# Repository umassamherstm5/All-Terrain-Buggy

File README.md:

# All-Terrain-Buggy
The All-Terrain Buggy is a buggy that goes on most if not all terrains. 

It is a 6-wheeled AWD remote controlled vehicle. The motors are driven by the DRV8871 motor drivers. 
The buggy is controlled via a FlySky remote that feeds PWM signals into an Adafruit Feather 328P MCU.  

This project contains the firmware for the Feather 328P and all KiCad files for the buggy's custom PCB.

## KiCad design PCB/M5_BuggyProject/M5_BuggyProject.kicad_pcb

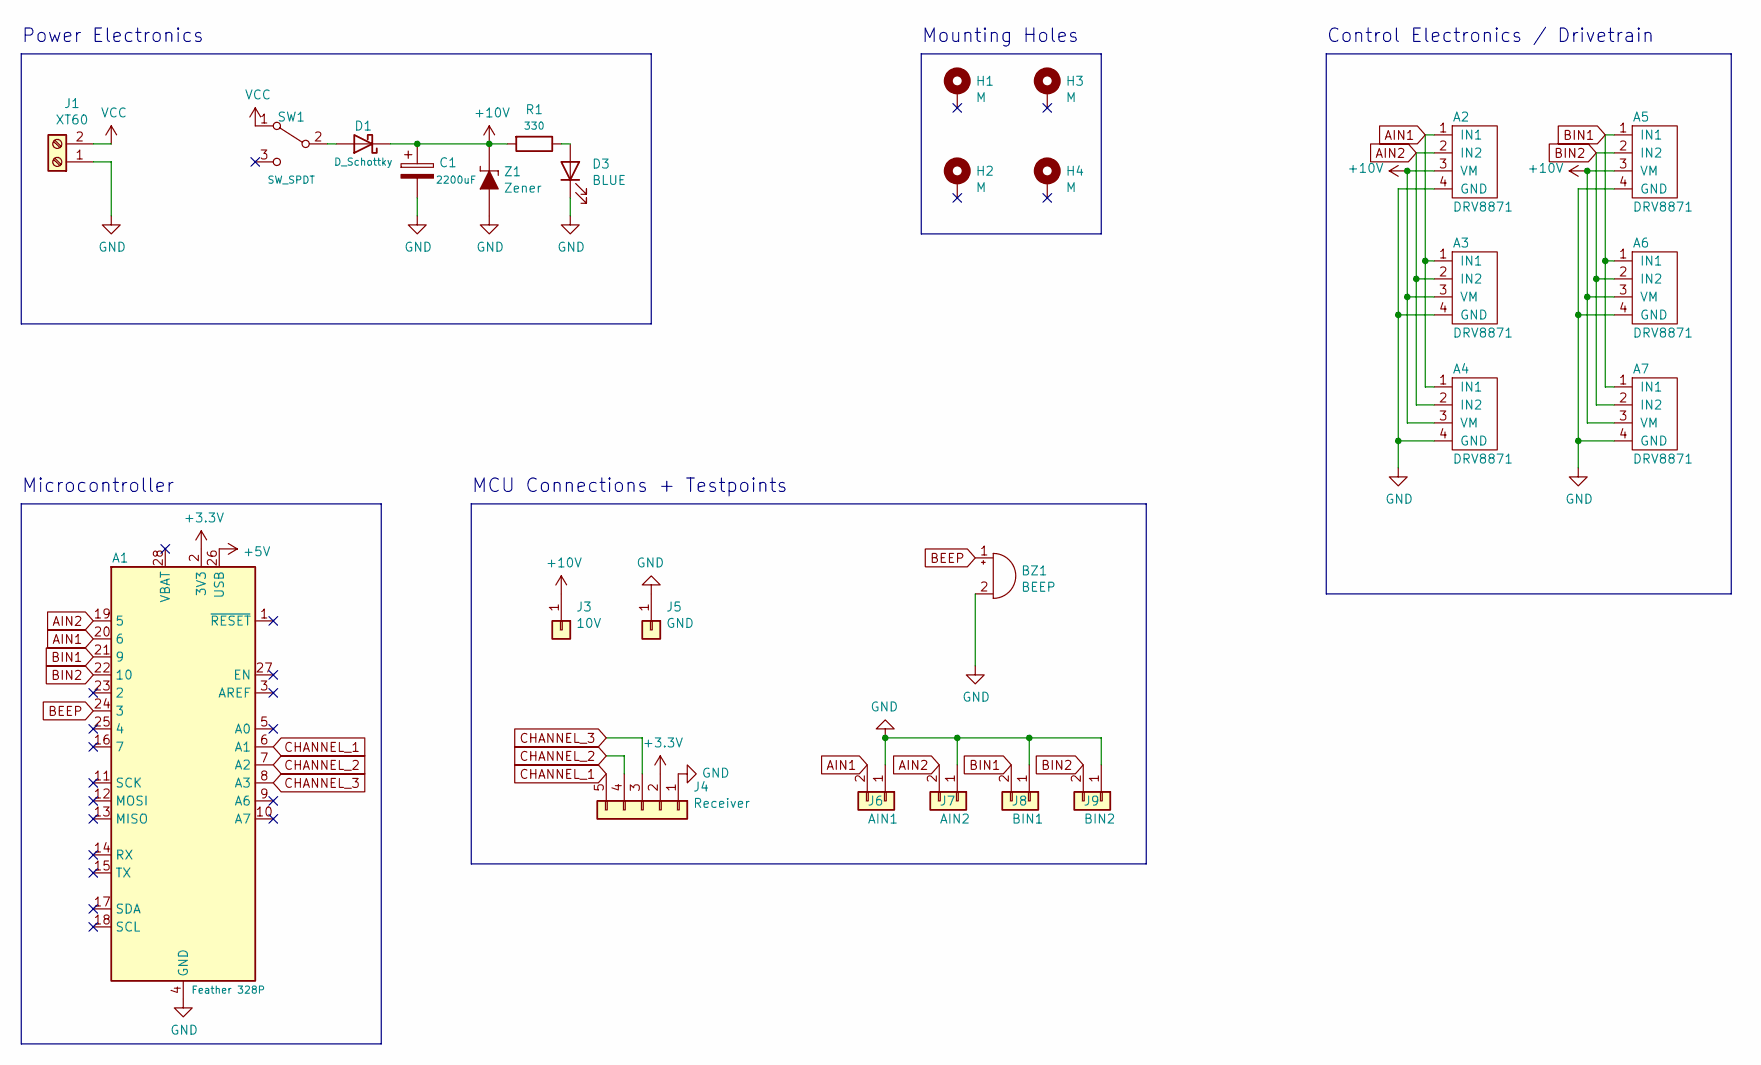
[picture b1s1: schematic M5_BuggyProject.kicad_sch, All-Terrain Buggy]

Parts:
A1: Feather 328P; Adafruit_Feather
A2, A3, A4, A5, A6, A7: DRV8871; PinSocket_1x04_P2.54mm_Vertical
BZ1: BEEP; Buzzer_12x9.5RM7.6
C1: 2200uF; CP_Radial_D10.0mm_P5.00mm
D1: D_Schottky; TO-220-2_Vertical
D3: BLUE; LED_1206_3216Metric
H1, H2, H3, H4: M; MountingHole_4.3mm_M4_Pad_Via
J1: XT60; AMASS_XT60-M_1x02_P7.20mm_Vertical
J3: 10V; TestPoint_Plated_Hole_D5.0mm
J4: Receiver; PinSocket_1x05_P2.54mm_Vertical
J5: GND; TestPoint_Plated_Hole_D5.0mm
J6: AIN1; PinSocket_1x02_P2.54mm_Vertical
J7: AIN2; PinSocket_1x02_P2.54mm_Vertical
J8: BIN1; PinSocket_1x02_P2.54mm_Vertical
J9: BIN2; PinSocket_1x02_P2.54mm_Vertical
R1: 330; R_1206_3216Metric
SW1: SW_SPDT; 1101M2S3CQE2
Z1: Zener; DO-214AC; MPN 1N5231BTR; Digi-Key_PN 1N5231BFSCT-ND

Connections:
+3V3: A1.2 (3V3), J4.2
+5V: A1.26 (USB)
+10V: A2.3 (VM), A3.3 (VM), A4.3 (VM), A5.3 (VM), A6.3 (VM), A7.3 (VM), C1.1, D1.1 (K), J3.1, R1.2, Z1.K
AIN1: A1.20 (6), A2.1 (IN1), A3.1 (IN1), A4.1 (IN1), J6.2
AIN2: A1.19 (5), A2.2 (IN2), A3.2 (IN2), A4.2 (IN2), J7.2
BEEP: A1.24 (3), BZ1.1 (-)
BIN1: A1.21 (9), A5.1 (IN1), A6.1 (IN1), A7.1 (IN1), J8.2
BIN2: A1.22 (10), A5.2 (IN2), A6.2 (IN2), A7.2 (IN2), J9.2
CHANNEL_1: A1.6 (A1), J4.5
CHANNEL_2: A1.7 (A2), J4.4
CHANNEL_3: A1.8 (A3), J4.3
GND: A1.4 (GND), A2.4 (GND), A3.4 (GND), A4.4 (GND), A5.4 (GND), A6.4 (GND), A7.4 (GND), BZ1.2 (+), C1.2, D3.1 (K), J1.1, J4.1, J5.1, J6.1, J7.1, J8.1, J9.1, Z1.A
unnamed: D1.2 (A), SW1.2 (B)
unnamed: D3.2 (A), R1.1
VCC: J1.2, SW1.1 (A)

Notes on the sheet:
MCU Connections + Testpoints
Control Electronics / Drivetrain
Power Electronics
Mounting Holes
Microcontroller

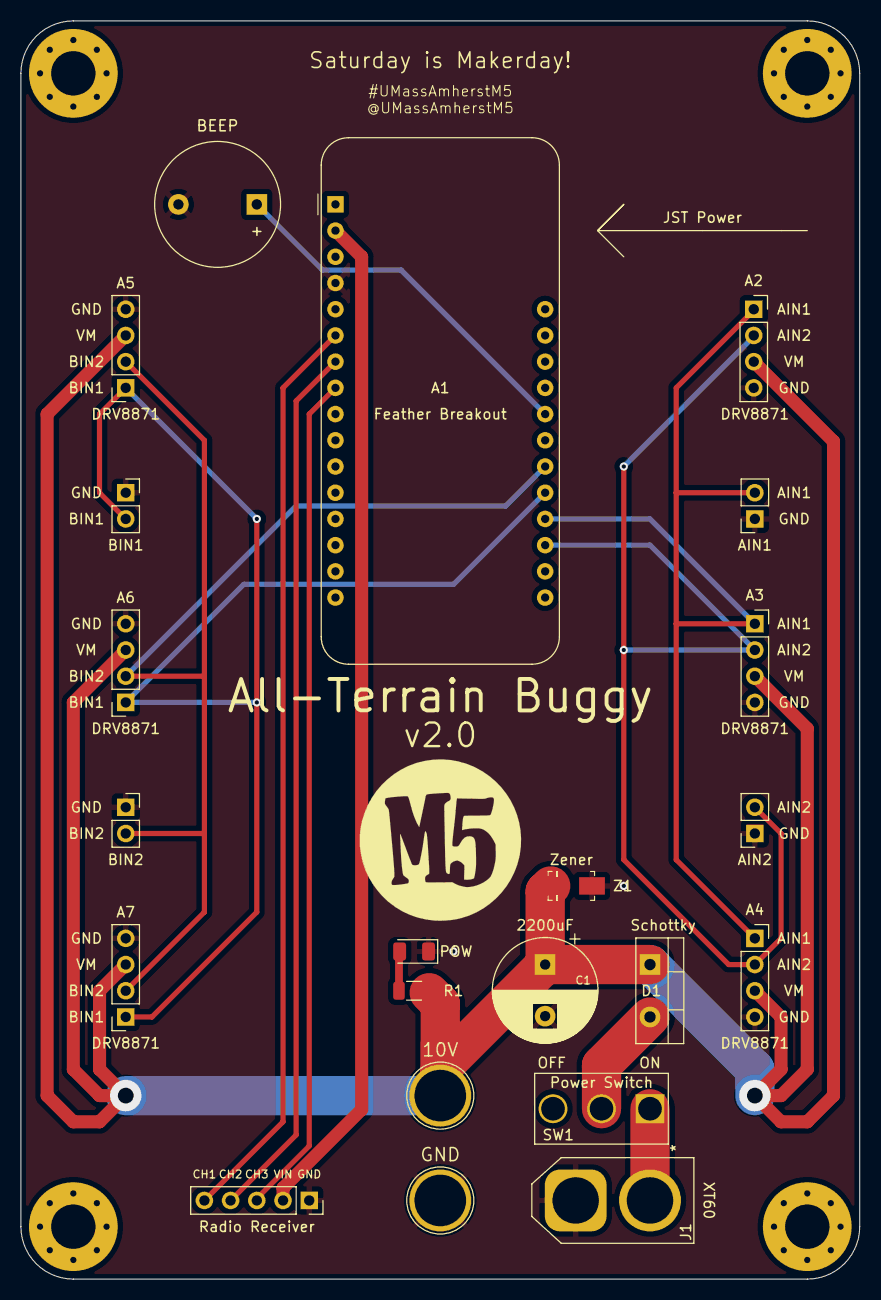
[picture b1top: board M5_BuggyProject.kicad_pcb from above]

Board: 2 copper layers, 81.3 x 121.9 mm, 26 parts (0 on the bottom side), 14 nets.

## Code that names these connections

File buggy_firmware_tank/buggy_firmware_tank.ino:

/*
 * All-Terrain Buggy
 * Firmware for interfacing with buggy and remote control 
 * Tank mode: each joystick controls each side
 * Authors: Akshat Sahay, Chris Caron, Sebastian Armstrong 
 */

/*
 * FlySky FS-GT
 * ------------
 * The FlySky FS-GT is a radio receiver module which pairs to a FlySky hobbyist controller. 
 * 
 * We connect this receiver to our Feather 328P and read the pulses on different channels using the pulseIn function. 
 * CHANNEL_1 refers to the left joystick's vertical motion. 
 * CHANNEL_2 refers to the right joystick's horizontal motion. 
 * CHANNEL_3 refers to the right pot 
 */

/* pin assignments for FlySky receiver signals */
#define CHANNEL_1 A1 // controller CH2  
#define CHANNEL_2 A2 // controller CH3
#define CHANNEL_3 A3

/*
 * DRV8871 Motor Driver 
 * --------------------
 * The DRV8871 is a brushed DC motor driver. Two logic inputs control 4 N-channel MOFSETs for bidirectional control. 
 * The inputs can be either HIGH/LOW or PWM (we use PWM and LOW) to control motor speed and direction. 
 * Setting both inputs to LOW activates a low-power deep sleep mode. This will help us conserve battery life. 
 * 
 * For ease of control, we connect each of the 3 motors on either side of the buggy together. 
 * This allows us to use only 4 pins on the Arduino instead of 12 (2 for each motor)
 * This also makes turning easy, as we simply slow down a side to turn in either direction. 
 * In the code, we refer to A as the right side and B as the left side. 
 * 
 * All inputs are PWM-capable pins 
 * AIN1 refers to input 1 for the right side. 
 * AIN2 refers to input 2 for the right side.
 * BIN1 refers to input 1 for the left side. 
 * BIN2 refers to input 2 for the left side. 
 */

/* pin assignments for driver control signals */
#define AIN1 6
#define AIN2 5 
#define BIN1 9
#define BIN2 10 

/*
 * We use pulseIn to read the pulse durations on CHANNEL_1 and CHANNEL_2. 
 * pulseIn detects a change on a pin (LOW->HIGH/HIGH->LOW). 
 * It measures the duration of the change and returns the duration in microseconds. 
 * 
 * The receiver pulses have default durations of about 1450us for CHANNEL_1 and 1475us for CHANNEL_2.  
 * Any shorter or longer pulses mean the joysticks are being used, and the buggy needs to perform an action. 
 * 
 * The threshold values are to check for the default durations: they act as a "deadzone" when the joysticks 
 * are in their central position. The car only performs actions when the durations are more than the 
 * "deadzone" values. 
 * 
 * We organise the buggy's action into 5 modes: STOP, FORWARD, BACKWARD, LEFT and RIGHT. 
 * Speed and vertical direction are controlled by the left joystick (sig1, CHANNEL_1). 
 * Horizontal direction is controlled by the right joystick (sig2, CHANNEL_2). 
 * 
 * STOP, FORWARD and BACKWARD are simple: the car stops, goes forward or backward. 
 * LEFT and RIGHT are a little more complex: in these modes the car goes in the direction specified, 
 * but the forward and backward motion is controlled within these conditions. 
*/

/* thresholds for signal values, used for identifying action and speed */
#define SIG_HIGH_ACC 1490
#define SIG_LOW_ACC 1410

#define SIG_HIGH_STEER 1515
#define SIG_LOW_STEER 1435

#define SIG_MAX_ACC 1850
#define SIG_MIN_ACC 1100

#define SIG_MAX_STEER 1950
#define SIG_MIN_STEER 1050

#define DEBUG 0  

/* variables for incoming pulse widths from CHANNEL_1 and CHANNEL_2 respectively */
int sig1 = 0; // CHANNEL_1 value
int sig2 = 0; // CHANNEL_2 value
int beep = 0; // to BEEP or not

/* variables for speed of either side */
int a_speed = 0; // speed of right side
int b_speed = 0; // speed of left side
int offset  = 0; // speed difference for turning

/* pins for debugging and BEEP */
#define BEEP 3
#define CONFIG_R A6
#define CONFIG_L A7

/*
 * Function: setup
 * ---------------
 * Runs once at the beginning of the code (when the buggy powers up or resets). 
 * Sets all required pin modes and begins the serial module. 
 * 
 * returns: none 
 */
void setup() {
  // set RC channels to INPUT
  pinMode(CHANNEL_1, INPUT); 
  pinMode(CHANNEL_2, INPUT); 

  // set driver pins to OUTPUT
  pinMode(AIN1, OUTPUT); 
  pinMode(AIN2, OUTPUT); 
  pinMode(BIN1, OUTPUT); 
  pinMode(BIN2, OUTPUT); 

  // set debugging pins to OUTPUT
  pinMode(BEEP, OUTPUT);
  pinMode(CONFIG_L, OUTPUT);
  pinMode(CONFIG_R, OUTPUT);

  // start serial port
  Serial.begin(9600);  
}

void loop() {
  // get signal values from receiver 
  sig1 = pulseIn(CHANNEL_1, HIGH);
  sig2 = pulseIn(CHANNEL_2, HIGH);

  if(((sig1 < SIG_HIGH_ACC) && (sig1 > SIG_LOW_ACC)) && ((sig2 < SIG_HIGH_STEER) && (sig2 > SIG_LOW_STEER))) {
    // both signals are OFF, state: STOP
    Serial.println("OFF"); 

    // set drivers to STOP mode 
    digitalWrite(AIN1, LOW);
    digitalWrite(AIN2, LOW); 
    digitalWrite(BIN1, LOW);
    digitalWrite(BIN2, LOW); 
  }

  if(sig1 > SIG_HIGH_ACC) {
    // sig1 is ON, state: RIGHT FORWARD
    Serial.println("RIGHT FORWARD"); 

    // limit sig1 values for speed
    if(sig1 > SIG_MAX_ACC) sig1 = SIG_MAX_ACC; 

    // get speed proportional to sig1 in FORWARD state
    // the higher the sig1 val, the higher the speed
    a_speed = map(sig1, SIG_HIGH_ACC, SIG_MAX_ACC, 0, 255);  

    // set drivers to FORWARD mode
    analogWrite(AIN1, a_speed);
    digitalWrite(AIN2, LOW); 
  }

  if(sig1 < SIG_LOW_ACC) {
    // sig1 is -ON, state: RIGHT BACKWARD
    Serial.println("RIGHT BACKWARD"); 

    // limit sig1 values for speed
    if(sig1 < SIG_MIN_ACC) sig1 = SIG_MIN_ACC;

    // get speed proportional to sig1 in BACKWARD state
    // the lower the sig1 val, the higher the speed
    a_speed = map(sig1, SIG_LOW_ACC, SIG_MIN_ACC, 0, 255); 

    // set driver to COUNTER-CLOCKWISE mode
    digitalWrite(AIN1, LOW);
    analogWrite(AIN2, a_speed);     
  }

  
}

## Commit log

2021-11-07 Initial Commit
    Added initial commit for interfacing with the FlySky receiver.
2021-11-09 Fixed getState conditionals
2021-11-09 Added driver code
    Added code for TB6612. FORWARD, BACKWARD, and RIGHT are fully implemented.
2021-11-09 Implemented all drive states
2021-11-09 Added spin modes
    Added spin mode for sig1 being OFF and sig2 being ON.
2021-11-16 Removed hardcoded thresholds
    Removed hardcoded thresholds for signal values.
2021-11-18 Fixed ERROR condition
2021-12-04 Added Documentation, Schematic
2022-01-07 Added KiCad Project, updated schematic
2022-01-09 Changed firmware, updated schematic and README
2022-01-11 Added updated netlist, started PCB
2022-01-11 Edited title blocks, netlist
2022-01-11 Added labels, traces for controls
2022-01-13 Updated PCB, added Digikey footprint library
2022-01-13 Added graphics to PCB
2022-01-19 Finalised PCB for v1.0
2022-01-27 Added gerber files
2022-01-30 Added social logos
2022-02-02 Added connector for radio receiver
2022-02-03 Moved back silkscreen contents
2022-02-10 Increased board size for trace width.
2022-02-12 Moved config LEDs, added OSH logo.
2022-02-13 Generated gerbers for v1.0
2022-03-02 Generated gerbers
2022-03-08 Updated PCB, removed gerbers
2022-04-26 Updated PCB, fixed speed thresholds in code.
2022-04-27 Fixed thresholds for movement
2022-05-18 Started PCB v2
2022-05-21 Added UMass logo, moved things around
2022-07-18 Updated PCB
2022-09-02 Updated document dates
2022-09-22 Imported to KiCad 6
    We're now in KiCad 6 land.

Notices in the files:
PCB/M5_BuggyProject/M5_BuggyProject.kicad_pcb:
creativecommons.org/licenses/by/4.0
License: CC BY 4.0
PCB/M5_BuggyProject/M5_BuggyProject.kicad_sch:
CC BY 4.0
parts and their libraries:
Copyright 2021 Accelerated Designs. All rights reserved.
